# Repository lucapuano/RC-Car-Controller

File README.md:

# RC Car Controller
The project consist of a simple RC car controller based on the popular STM32F103C8T6, programmable through the usb port by the FT232RL.
There are two connector, one for the servo motor and the other for the ESC.  
The whole circuit is powered by the ESC connector.
Current version: V2
## PCB Screenshots
### Layers view

### 3D view

## UPDATES
- Improved the design and traces
- Solved some issues and errors in design

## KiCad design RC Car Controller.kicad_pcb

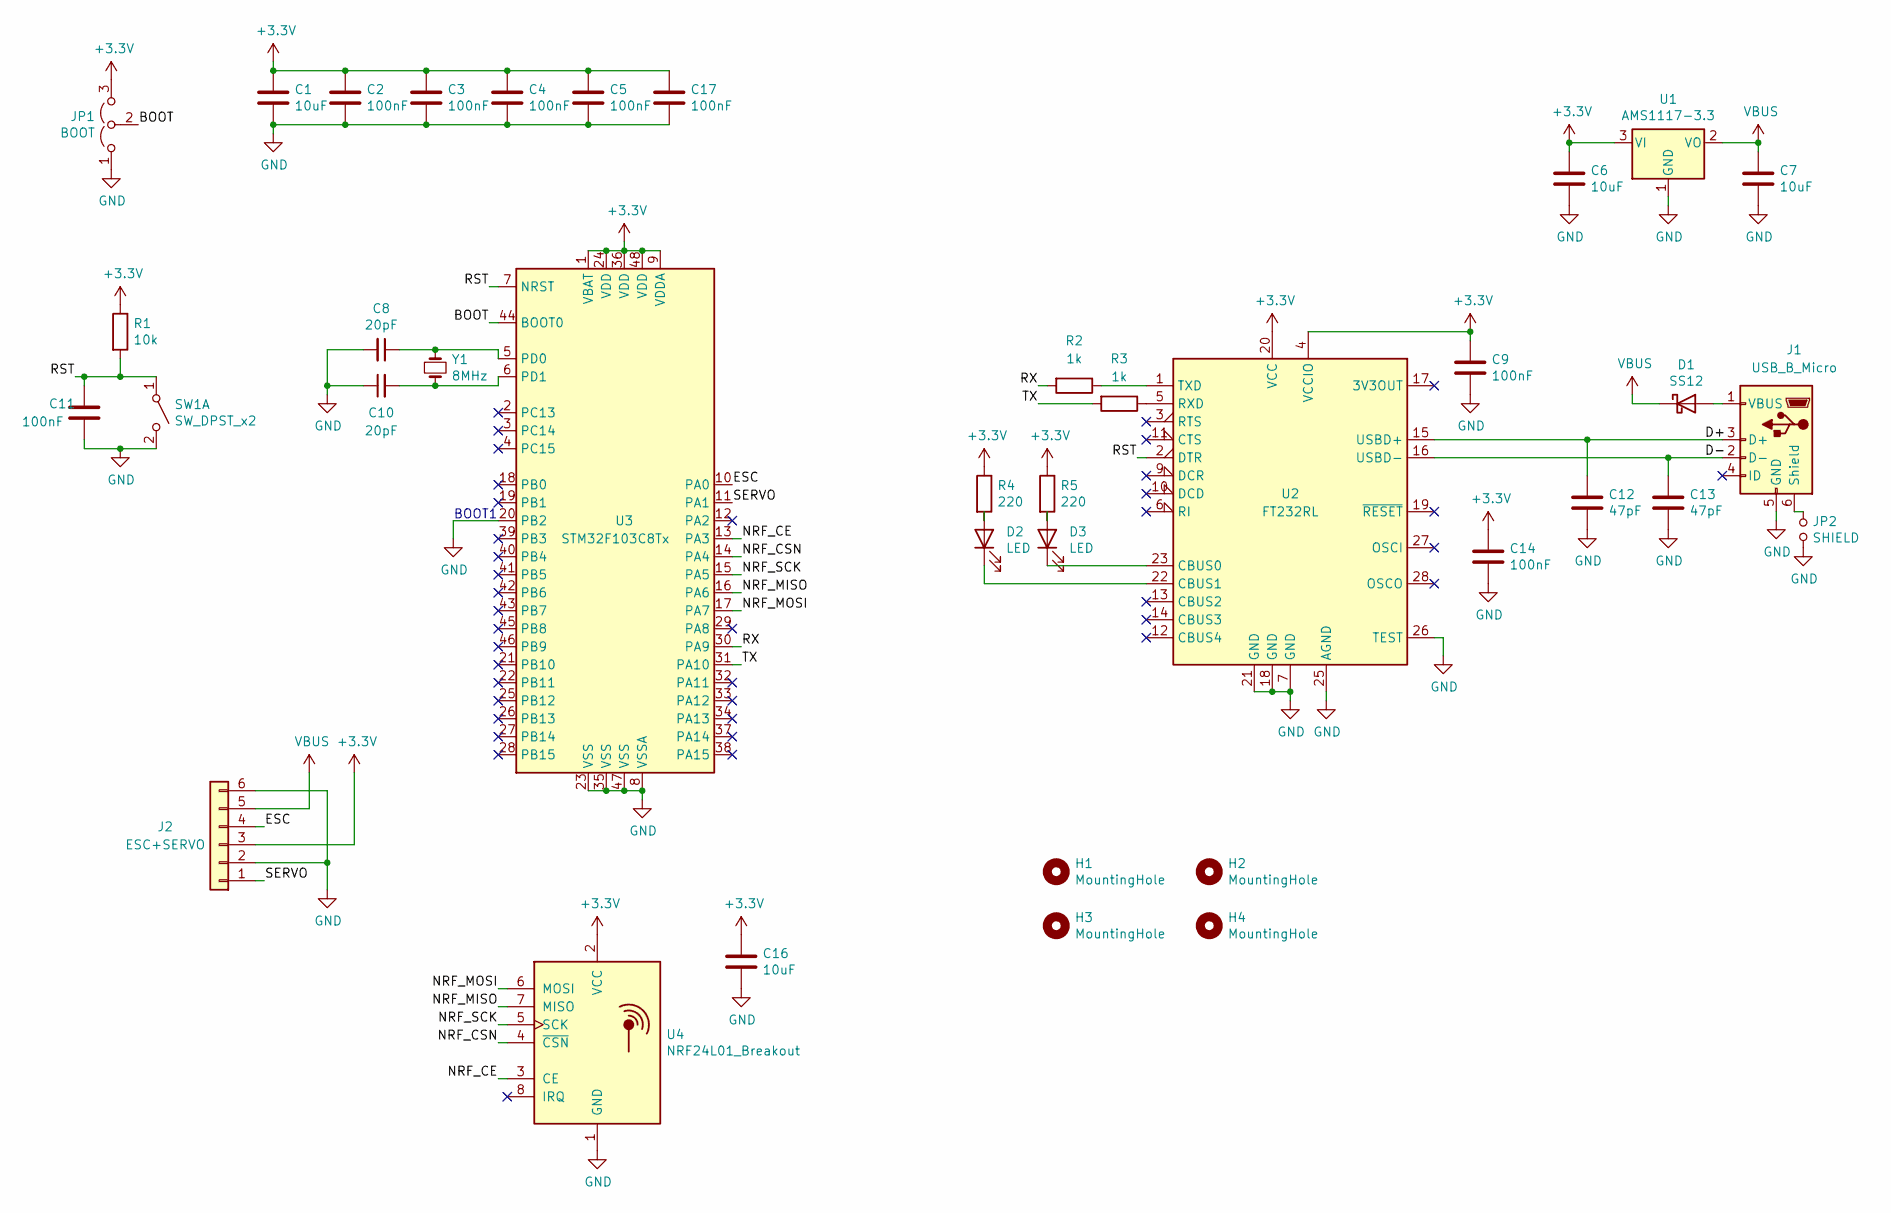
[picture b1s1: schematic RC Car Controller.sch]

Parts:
C1, C6, C7, C16: 10uF; C_0805_2012Metric
C2, C3, C4, C5, C9, C11, C14, C17: 100nF; C_0603_1608Metric
C8, C10: 20pF; C_0603_1608Metric
C12, C13: 47pF; C_0603_1608Metric
D1: SS12; D_SMA
D2, D3: LED; LED_0603_1608Metric
H1, H2, H3, H4: MountingHole; MountingHole_3mm
J1: USB_B_Micro; USB_Micro-B_Wuerth_629105150521
J2: ESC+SERVO; PinHeader_1x06_P2.54mm_Vertical
JP1: BOOT; PinHeader_1x03_P2.54mm_Vertical
JP2: SHIELD; SolderJumper-2_P1.3mm_Open_RoundedPad1.0x1.5mm
R1: 10k; R_0603_1608Metric
R2, R3: 1k; R_0603_1608Metric
R4, R5: 220; R_0603_1608Metric
SW1: SW_DPST_x2; SW_PUSH_6mm
U1: AMS1117-3.3; SOT-223-3_TabPin2
U2: FT232RL; SSOP-28_5.3x10.2mm_P0.65mm
U3: STM32F103C8Tx; LQFP-48_7x7mm_P0.5mm
U4: NRF24L01_Breakout; NRF24L01 LA PNA
Y1: 8MHz; Crystal_SMD_5032-2Pin_5.0x3.2mm

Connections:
+3V3: C1.1, C2.1, C3.1, C4.1, C5.1, C6.1, C9.1, C14.1, C16.1, C17.1, J2.3, JP1.3 (B), R1.1, R4.1, R5.1, U1.3 (VI), U2.4 (VCCIO), U2.20 (VCC), U3.1 (VBAT), U3.9 (VDDA), U3.24 (VDD), U3.36 (VDD), U3.48 (VDD), U4.2 (VCC)
/BOOT: JP1.2 (C), U3.44 (BOOT0)
/D+: C12.1, J1.3 (D+), U2.15 (USBD+)
/D-: C13.1, J1.2 (D-), U2.16 (USBD-)
/ESC: J2.4, U3.10 (PA0)
/NRF_CE: U3.13 (PA3), U4.3 (CE)
/NRF_CSN: U3.14 (PA4), U4.4 (~CSN)
/NRF_MISO: U3.16 (PA6), U4.7 (MISO)
/NRF_MOSI: U3.17 (PA7), U4.6 (MOSI)
/NRF_SCK: U3.15 (PA5), U4.5 (SCK)
/RST: C11.1, R1.2, SW1.1 (A), U2.2 (DTR), U3.7 (NRST)
/RX: R2.2, U3.30 (PA9)
/SERVO: J2.1, U3.11 (PA1)
/TX: R3.2, U3.31 (PA10)
GND: C1.2, C2.2, C3.2, C4.2, C5.2, C6.2, C7.2, C8.2, C9.2, C10.1, C11.2, C12.2, C13.2, C14.2, C16.2, C17.2, J1.5 (GND), J2.2, J2.6, JP1.1 (A), JP2.2, SW1.2 (B), U1.1 (GND), U2.7 (GND), U2.18 (GND), U2.21 (GND), U2.25 (AGND), U2.26 (TEST), U3.8 (VSSA), U3.20 (PB2), U3.23 (VSS), U3.35 (VSS), U3.47 (VSS), U4.1 (GND)
unnamed: C8.1, U3.5 (PD0), Y1.1
unnamed: C10.2, U3.6 (PD1), Y1.2
unnamed: D1.2 (A), J1.1 (VBUS)
unnamed: D2.1 (K), U2.22 (CBUS1)
unnamed: D2.2 (A), R4.2
unnamed: D3.1 (K), U2.23 (CBUS0)
unnamed: D3.2 (A), R5.2
unnamed: J1.6 (Shield), JP2.1
unnamed: R2.1, U2.1 (TXD)
unnamed: R3.1, U2.5 (RXD)
VBUS: C7.1, D1.1 (K), J2.5, U1.2 (VO)

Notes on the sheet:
BOOT1

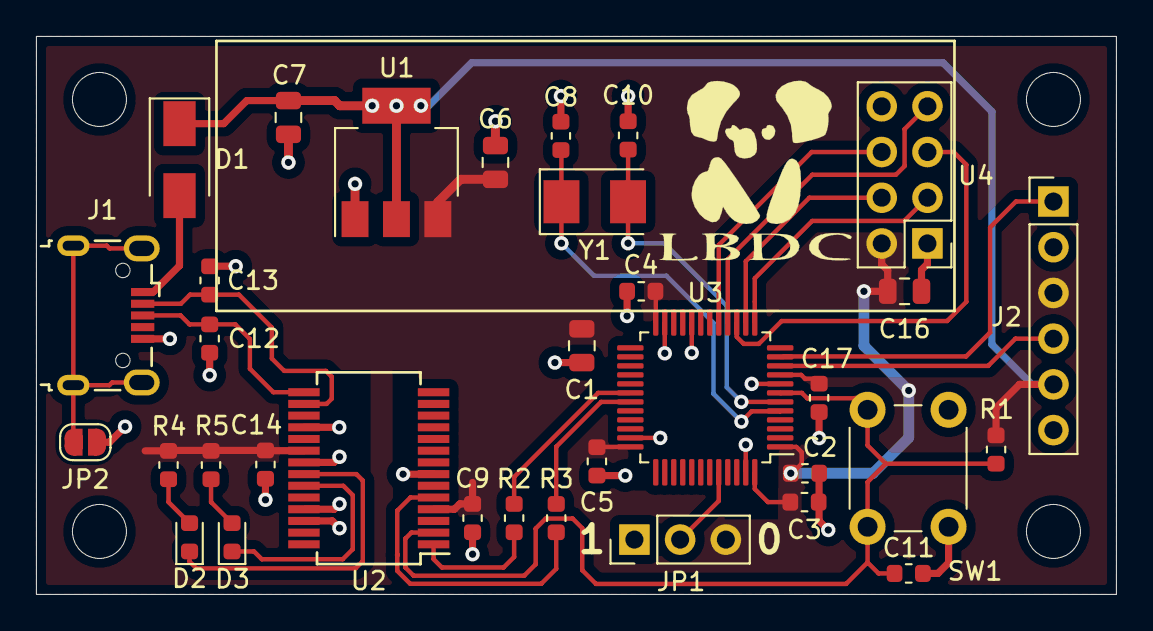
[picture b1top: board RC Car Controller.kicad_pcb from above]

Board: 2 copper layers, 60.0 x 31.0 mm, 38 parts (0 on the bottom side), 26 nets.

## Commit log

2020-07-19 Add files via upload
    Added all the kicad project, with gerber and 3d model
2020-07-19 Create Pictures
